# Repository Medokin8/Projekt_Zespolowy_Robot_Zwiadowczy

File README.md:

#Projekt_Zespolowy_Robot_Zwiadowczy
Repozytorium dla Projektu Zespołowego - Robot Zwiadowczy

Link do strony, poświęconej projektowi: http://panamint.kcir.pwr.edu.pl/~niwin/

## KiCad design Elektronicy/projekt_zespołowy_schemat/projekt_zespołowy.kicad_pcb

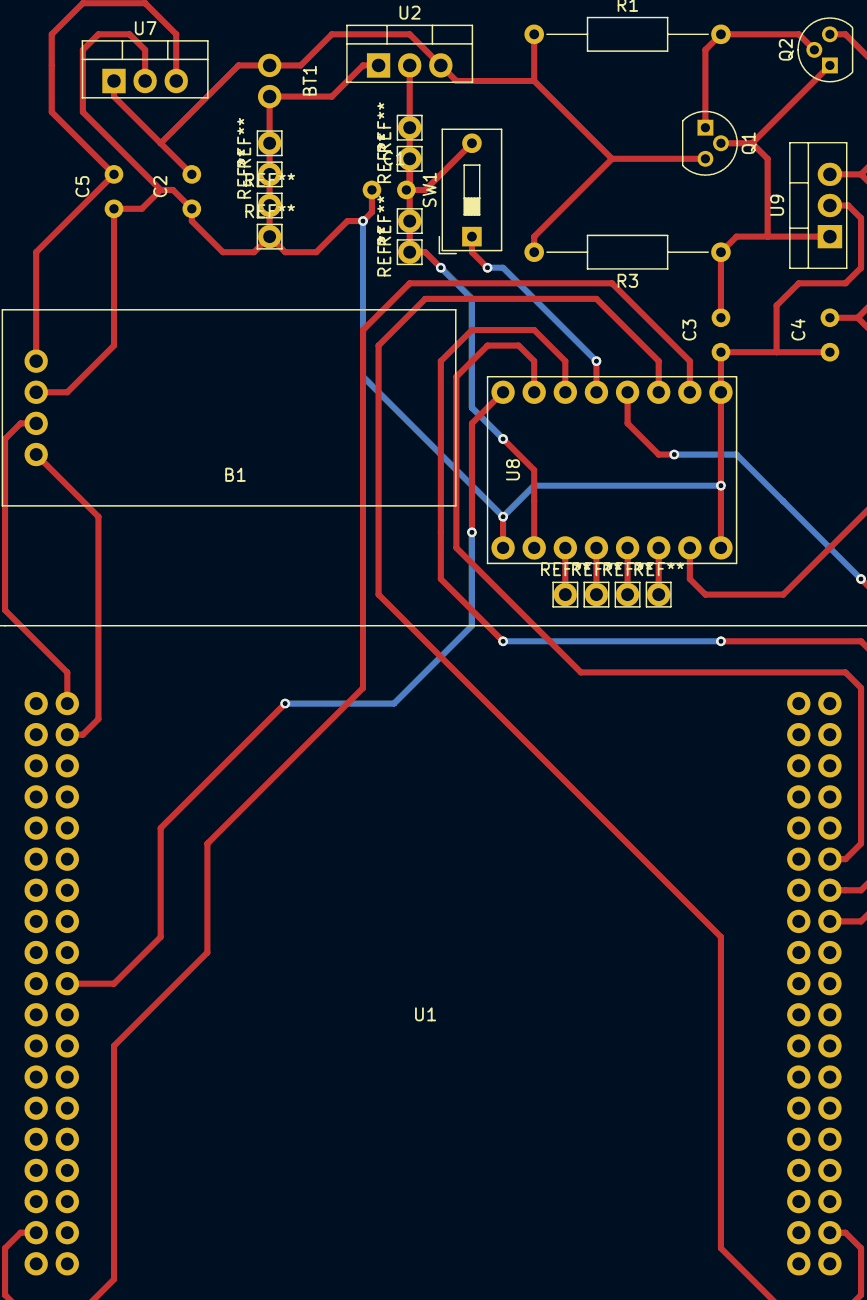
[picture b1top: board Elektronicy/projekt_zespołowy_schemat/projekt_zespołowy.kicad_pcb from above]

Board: 2 copper layers, 17 parts (0 on the bottom side), 16 nets.

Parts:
B1: HC-06_ZS-040-projekt_zespolowy; HC-06_ZS-040
BT1: Battery_Cell; bat
C1, C4, C5: 100n; C
C2, C3: 330n; C
Q1, Q2: Q_PNP_BCE; TO-92
R1: 15m; R_Axial_DIN0207_L6.3mm_D2.5mm_P15.24mm_Horizontal
R3: 3; R_Axial_DIN0207_L6.3mm_D2.5mm_P15.24mm_Horizontal
SW1: SW_DIP_x01; SW_DIP_SPSTx01_Slide_9.78x4.72mm_W7.62mm_P2.54mm
U1: STM32F334R8Tx; stm32f334R8
U2: LD1117S33TR_SOT223; TO-220-3_Vertical
U7: L7805; TO-220-3_Vertical
U8: TB6612FNG-projekt_zespolowy; TB6612FNG
U9: LM7808_TO220; TO-220-3_Vertical

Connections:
+3V3: C1.1, SW1.2, U2.2, U8.2
AIN1: U1.3, U8.11
AIN2: U1.4, U8.10
BIN1: U1.2, U8.13
BIN2: U1.53, U8.14
GND: B1.3, BT1.2, C1.2, C2.2, C3.2, C4.2, C5.2, U2.1, U7.2, U8.1, U8.8, U8.16, U9.2
unnamed: C3.1, Q1.2, Q2.1, R3.1, U9.1
unnamed: Q1.1, Q2.2, R1.2
PWMA: U1.38, U8.9
PWMB: U1.37, U8.15
RX: B1.1, U1.16
STBY: SW1.1, U8.12
TX: B1.2, U1.17
VCC: B1.4, C5.1, U7.3
VMOT: BT1.1, C2.1, Q1.3, R1.1, R3.2, U2.3, U7.1
VMOTS: C4.1, Q2.3, U8.7, U9.3

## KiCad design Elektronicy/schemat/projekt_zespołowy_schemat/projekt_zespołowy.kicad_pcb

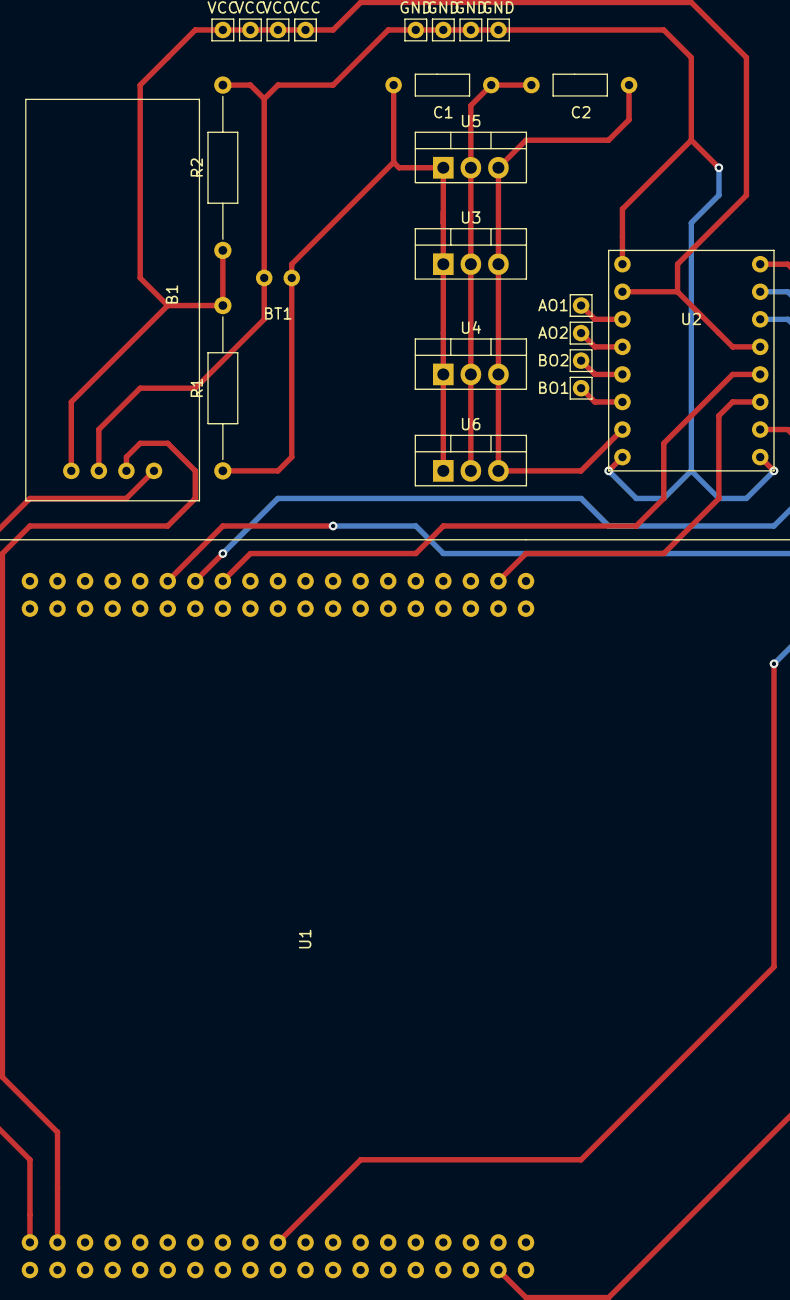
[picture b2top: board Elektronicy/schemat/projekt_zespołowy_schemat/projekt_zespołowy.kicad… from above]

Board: 2 copper layers, 24 parts (0 on the bottom side), 13 nets.

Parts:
AO1, AO2: pin
B1: HC-06_ZS-040
BO1, BO2: pin
BT1: Battery_Cell; bat
C1, C2: 100n; C
GND: pin
GND#2, GND#3, GND#4: pin
R1: 236; R_Axial_DIN0207_L6.3mm_D2.5mm_P15.24mm_Horizontal
R2: 100; R_Axial_DIN0207_L6.3mm_D2.5mm_P15.24mm_Horizontal
U1: STM32F334R8Tx; stm32f334R8
U2: TB6612FNG
U3, U4, U5, U6: LM7808_TO220; TO-220-3_Vertical
VCC: pin
VCC#2, VCC#3, VCC#4: pin

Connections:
AIN1: U1.3, U2.11
AIN2: U1.4, U2.10
BIN1: U1.2, U2.13
BIN2: U1.53, U2.14
GND: B1.3, BT1.2, GND.1, GND#2.1, GND#3.1, GND#4.1, R2.2, U2.1, U2.8, U2.16
unnamed: C1.1, C2.2, U3.2, U4.2, U5.2, U6.2
PWMA: U1.38, U2.9
PWMB: U1.37, U2.15
RX: B1.1, U1.17
TX: B1.2, U1.16
VCC: B1.4, R1.2, R2.1, U2.2, U2.12, VCC.1, VCC#2.1, VCC#3.1, VCC#4.1
VMOT: BT1.1, C1.2, R1.1, U3.1, U4.1, U5.1, U6.1
VMOTS: C2.1, U2.7, U3.3, U4.3, U5.3, U6.3

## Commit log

2022-03-25 Rename README.md.txt to README.md
2022-03-27 v0.0.1
    Dodano dokumentację techniczną i przydatne linki dotyczące zamówionych części.
2022-03-27 v0.0.2
    Elektronicy - dodano pierwszy raport
2022-04-10 v0.1.0
    dodano:
    -schemat połączeń elektronicznych
    -projekt płytki pcb
2022-04-10 Raport 2
2022-04-10 raport 2
    dodano raport 2
2022-05-15 zdjęcia układu
2022-05-15 raport 3
2022-06-01 kod stm32
2022-06-05 schemat końcowy
2022-06-05 raport 4
